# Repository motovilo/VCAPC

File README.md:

# VCAPC
 Voltage Controlled Atari Punk Console

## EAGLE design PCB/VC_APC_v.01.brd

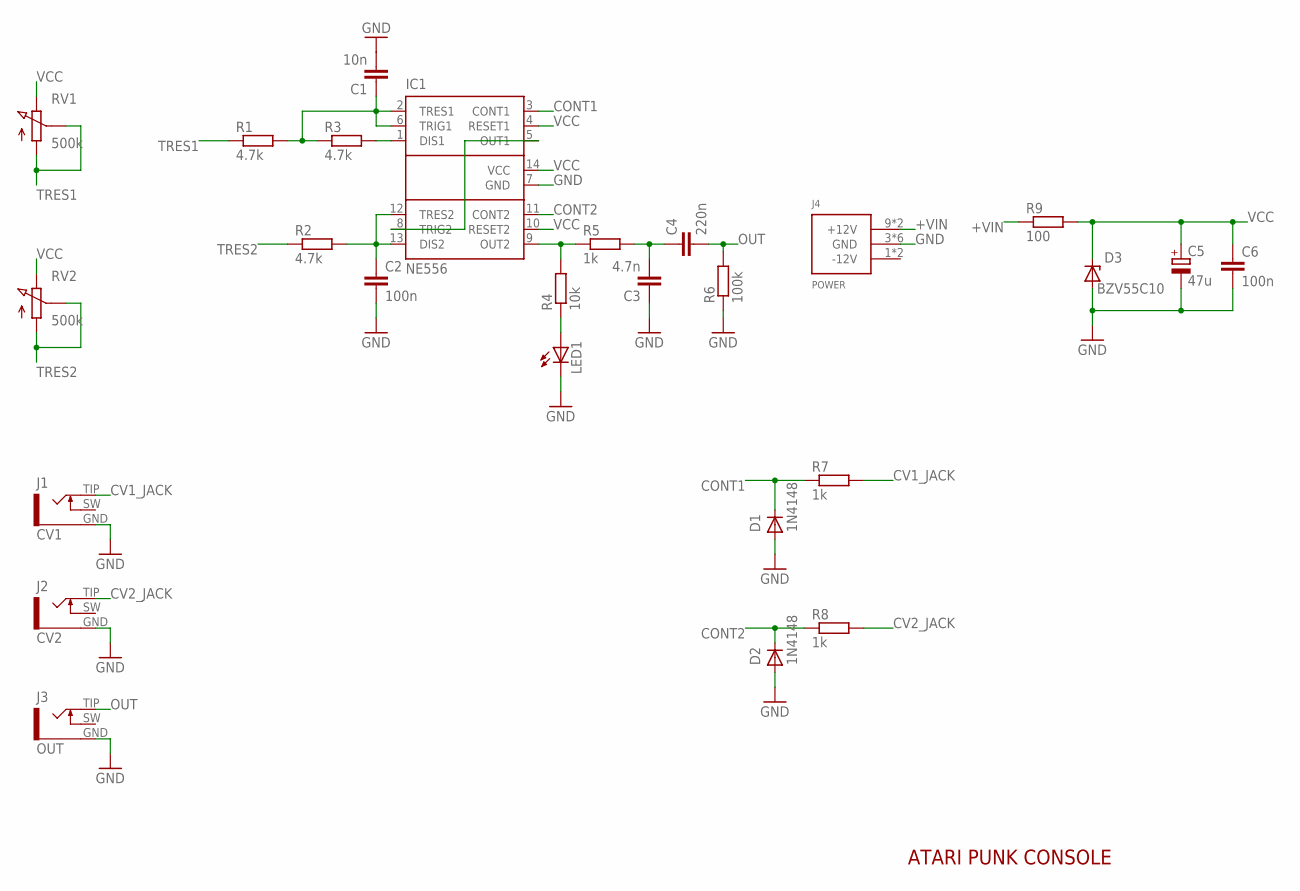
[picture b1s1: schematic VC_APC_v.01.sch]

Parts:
C1: 10n; C050-025X075
C2, C6: 100n; C050-025X075
C3: 4.7n; C050-025X075
C4: 220n; C050-025X075
C5: 47u; E2,5-6
D1, D2: 1N4148; DO35-7
D3: BZV55C10; DO35-7@1
IC1: NE556; DIL14
J1: CV1; WQP-PJ302M
J2: CV2; WQP-PJ302M
J3: OUT; WQP-PJ302M
J4: POWER; POWER_10M
LED1: LED3MM
R1, R2, R3: 4.7k; 0204/7
R4: 10k; 0204/7
R5, R7, R8: 1k; 0204/7
R6: 100k; 0204/7
R9: 100; 0204/7
RV1, RV2: 500k; POT_RK097N

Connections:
+VIN: J4.9 (+12V), J4.10 (+12V), R9.1
CONT1: D1.C, IC1.3 (CONT1), R7.1
CONT2: D2.C, IC1.11 (CONT2), R8.1
CV1_JACK: J1.TIP, R7.2
CV2_JACK: J2.TIP, R8.2
DIS1: IC1.1 (DIS1), R3.2
GND: C1.2, C2.2, C3.1, C5.-, C6.2, D1.A, D2.A, D3.A, IC1.7 (GND), J1.GND, J2.GND, J3.GND, J4.3 (GND), J4.4 (GND), J4.5 (GND), J4.6 (GND), J4.7 (GND), J4.8 (GND), LED1.K (C), R6.1
unnamed: LED1.A, R4.1
OUT: C4.2, J3.TIP, R6.2
OUT1: IC1.5 (OUT1), IC1.8 (TRIG2)
OUT_: IC1.9 (OUT2), R4.2, R5.1
OUT_LP: C3.2, C4.1, R5.2
TRES1: R1.1, RV1.1, RV1.2
TRES1_: C1.1, IC1.2 (TRES1), IC1.6 (TRIG1), R1.2, R3.1
TRES2: R2.1, RV2.1, RV2.2
TRES2_: C2.1, IC1.12 (TRES2), IC1.13 (DIS2), R2.2
VCC: C5.+, C6.1, D3.C, IC1.4 (RESET1), IC1.10 (RESET2), IC1.14 (VCC), R9.2, RV1.3, RV2.3

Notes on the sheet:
ATARI PUNK CONSOLE

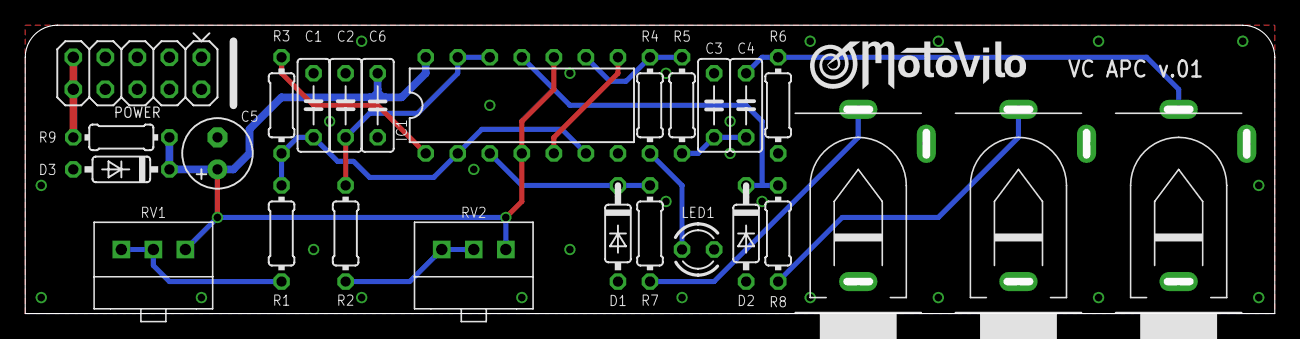
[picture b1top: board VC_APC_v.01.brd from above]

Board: 2 copper layers, 98.5 x 22.3 mm, 27 parts (0 on the bottom side), 17 nets.

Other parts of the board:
U$1: LOGO_SPACE_002

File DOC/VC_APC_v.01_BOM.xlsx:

Parts | Qty | Value | Device | Package | Description
LED1 | 1 |  | LED3MM | LED3MM | LED BLUE
R9 | 1 | 100 | R-EU_0204/7 | 0204/7 | RESISTOR, European symbol
R6 | 1 | 100k | R-EU_0204/7 | 0204/7 | RESISTOR, European symbol
C2, C6 | 2 | 100n | C-EU050-025X075 | C050-025X075 | CAPACITOR, European symbol
R4 | 1 | 10k | R-EU_0204/7 | 0204/7 | RESISTOR, European symbol
C1 | 1 | 10n | C-EU050-025X075 | C050-025X075 | CAPACITOR, European symbol
D1, D2 | 2 | 1N4148 | 1N4148DO35-7 | DO35-7 | DIODE
R5, R7, R8 | 3 | 1k | R-EU_0204/7 | 0204/7 | RESISTOR, European symbol
C4 | 1 | 220n | C-EU050-025X075 | C050-025X075 | CAPACITOR, European symbol
R1, R2, R3 | 3 | 4.7k | R-EU_0204/7 | 0204/7 | RESISTOR, European symbol
C3 | 1 | 4.7n | C-EU050-025X075 | C050-025X075 | CAPACITOR, European symbol
C5 | 1 | 47u | CPOL-EUE2.5-6 | E2,5-6 | POLARIZED CAPACITOR, European symbol
RV1, RV2 | 2 | 500k | POT_RK | POT_RK097N | POT one level
D3 | 1 | BZV55C10 | ZENERDO35 | DO35-7@1 | ZENER DIODE
J1 | 1 | CV1 | JACK_MONOSWH | WQP-PJ302M
J2 | 1 | CV2 | JACK_MONOSWH | WQP-PJ302M
IC1 | 1 | NE556 | NE556 | DIL14 | General Purpose Biopolartimer
J3 | 1 | OUT | JACK_MONOSWH | WQP-PJ302M
J4 | 1 | POWER | POWER_SIMPLEM | POWER_10M | Eororack Power Connector 10 Pin
